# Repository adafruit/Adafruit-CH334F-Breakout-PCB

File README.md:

## Adafruit CH334F Mini USB Hub Breakouts PCB

<a href="http://www.adafruit.com/products/5997"><br/>
Click here to purchase one from the Adafruit shop</a>
<br>
<a href="http://www.adafruit.com/products/5999"><br/>
Click here to purchase one from the Adafruit shop</a>

PCB files for the Adafruit CH334F Mini USB Hub Breakouts

Format is EagleCAD schematic and board layout
* https://www.adafruit.com/product/5997
* https://www.adafruit.com/product/5999

### Description

Sometimes you've got something with USB host, like a embedded linux board, and you want to connect more than one thing. Or maybe you want to turn something like a keyboard into a multi-device USB peripheral. The Adafruit CH334F Mini 4-Port USB Hub Breakout will do that for you! it features a CH334F USB 2.1 hub chip which converts one high-speed port into four.

Most folks who use a USB hub get one that comes in an enclosure with connectors or cables included. But, those hubs are going to be bulky - they're meant for external use. This breakout board is designed to be compact, so it can easily be embedded into an enclosure or existing device. There's four mounting holes but other than that, we tried to keep it as compact as possible.

Part of how we kept it small is not including downstream ports! The breakout has either 0.1" header or USB C for the upstream, and then four 4-pin ports for peripheral connections. We expect folks to solder directly to the pads or use our 'simple' USB-breakout cables.

You get one fully assembled/tested boards and some extra header if you happen to want to plug it into a breadboard. Other than that, just keep in mind there's no USB ports for the 4 downstreams - if you need those take a look at some of the other hubs we stock.

### License

Adafruit invests time and resources providing this open source design, please support Adafruit and open-source hardware by purchasing products from [Adafruit](https://www.adafruit.com)!

Designed by Limor Fried/Ladyada for Adafruit Industries.

Creative Commons Attribution/Share-Alike, all text above must be included in any redistribution. 
See license.txt for additional details.

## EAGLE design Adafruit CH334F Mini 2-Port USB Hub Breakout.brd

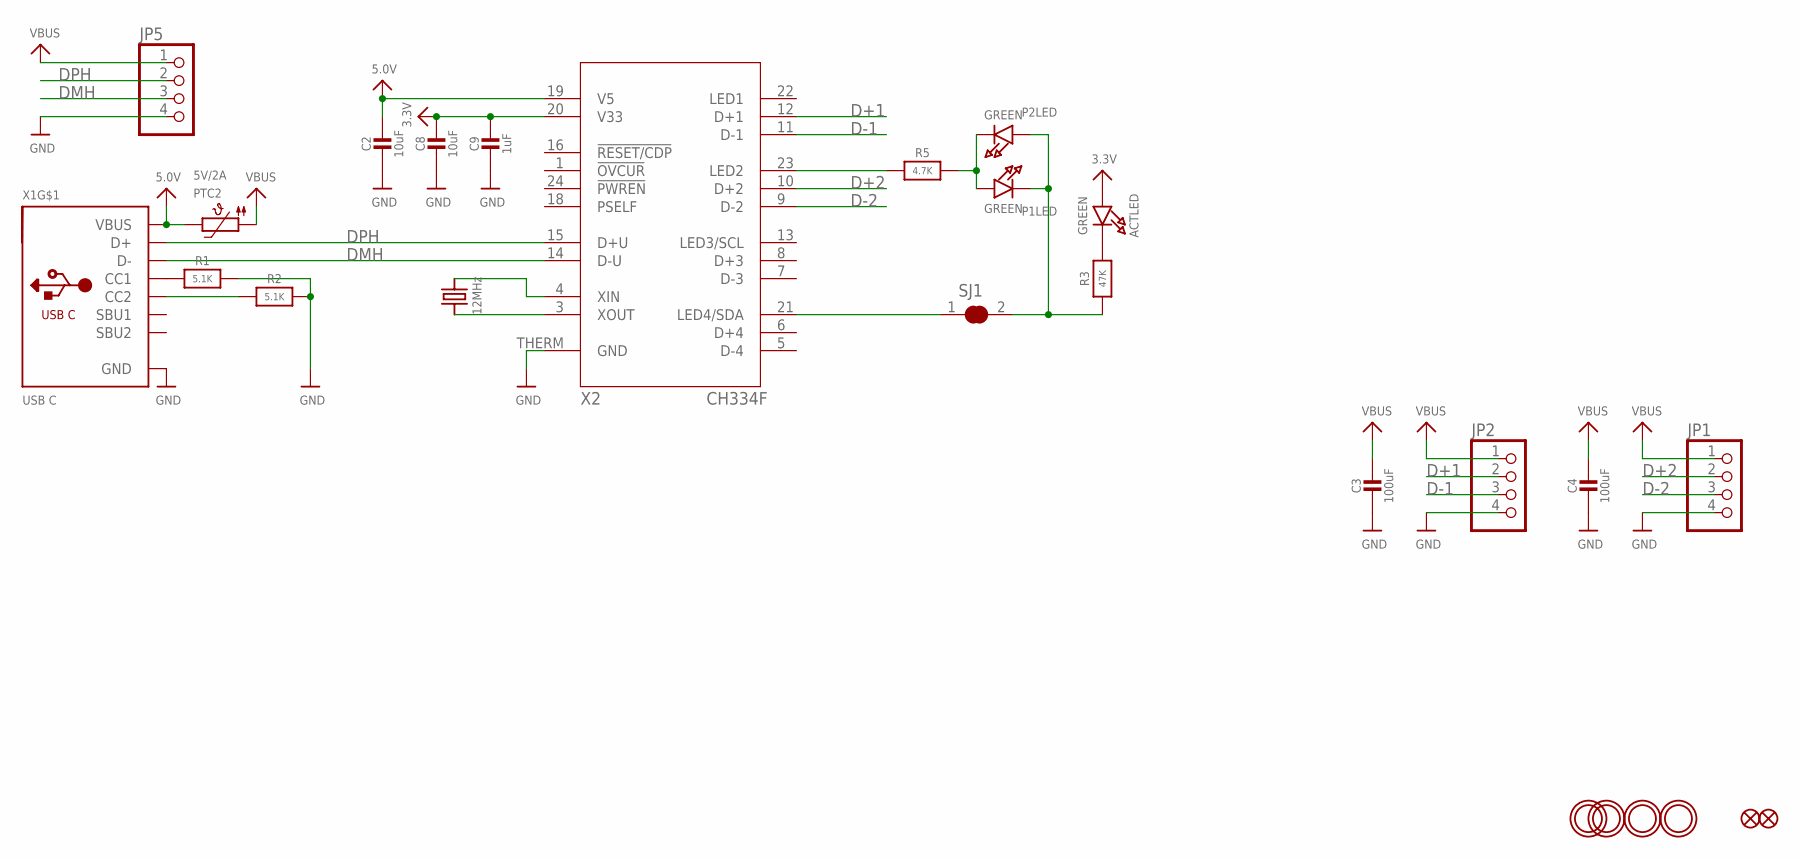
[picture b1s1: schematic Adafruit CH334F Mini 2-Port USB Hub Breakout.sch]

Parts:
ACTLED: GREEN; CHIPLED_0603_NOOUTLINE
C2, C8: 10uF; 0805-NO
C3, C4: 100uF; _1206
C9: 1uF; 0603-NO
FID1, FID2: FIDUCIAL_0.5MM
JP1, JP2, JP5: HEADER-1X4ROUND; 1X04_ROUND
P1LED, P2LED: GREEN; CHIPLED_0603_NOOUTLINE
PTC2: 5V/2A; 0805-NO
R1, R2: 5.1K; 0603-NO
R3: 47K; 0603-NO
R5: 4.7K; 0603-NO
SJ1: SOLDERJUMPER_CLOSED; SOLDERJUMPER_CLOSEDWIRE
U$23, U$28, U$29, U$31: MOUNTINGHOLE2.5; MOUNTINGHOLE_2.5_PLATED
X1: USB C; USB_C_CUSB31-CFM2AX-01-X
X2: CH334F; QFN24_4MM
Y1: 12MHz; CRYSTAL_2.5X2

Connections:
3.3V: ACTLED.A, C8.1, C9.1, X2.20 (V33)
5.0V: C2.1, PTC2.2, X1.A4B9 (VBUS), X1.B4A9 (VBUS), X2.19 (V5)
D+1: JP2.2, X2.12 (D+1)
D+2: JP1.2, X2.10 (D+2)
D-1: JP2.3, X2.11 (D-1)
D-2: JP1.3, X2.9 (D-2)
DMH: JP5.3, X1.A7 (D-), X1.B7 (D-), X2.14 (D-U)
DPH: JP5.2, X1.A6 (D+), X1.B6 (D+), X2.15 (D+U)
GND: C2.2, C3.2, C4.2, C8.2, C9.2, JP1.4, JP2.4, JP5.4, R1.2, R2.2, X1.A1B12 (GND), X1.B1A12 (GND), X2.THERM (GND)
unnamed: R1.1, X1.A5 (CC1)
unnamed: R2.1, X1.B5 (CC2)
unnamed: X2.3 (XOUT), Y1.1
unnamed: X2.4 (XIN), Y1.3 (2)
unnamed: ACTLED.C, R3.2
unnamed: P1LED.C, P2LED.A, R3.1, SJ1.2
unnamed: SJ1.1, X2.21 (LED4/SDA)
unnamed: P1LED.A, P2LED.C, R5.2
unnamed: R5.1, X2.23 (LED2)
VBUS: C3.1, C4.1, JP1.1, JP2.1, JP5.1, PTC2.1

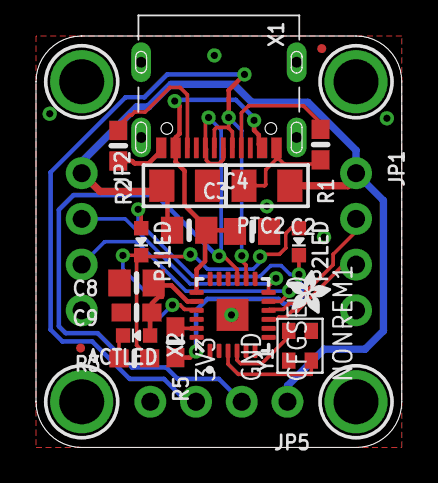
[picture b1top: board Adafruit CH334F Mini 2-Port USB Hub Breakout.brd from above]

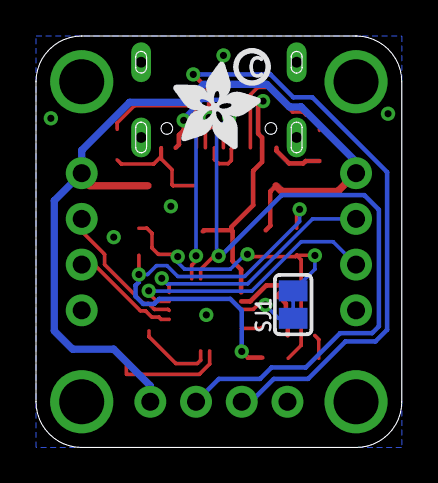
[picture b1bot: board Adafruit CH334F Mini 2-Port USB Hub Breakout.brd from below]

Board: 2 copper layers, 20.3 x 22.9 mm, 49 parts (9 on the bottom side), 19 nets.

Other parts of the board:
PLABEL0: PLABEL0
PLABEL1: PLABEL1
PLABEL3: PLABEL3
PLABEL5: PLABEL5
PLABEL6: PLABEL6
PLABEL7: PLABEL7
PLABEL8: PLABEL8
PLABEL11: PLABEL11
PLABEL13: PLABEL13
PLABEL19: PLABEL19
PLABEL21: PLABEL21
PLABEL22: PLABEL22
PLABEL23: PLABEL23
PLABEL24: PLABEL24
PLABEL26: PLABEL26
PLABEL27: PLABEL27
PLABEL30: PLABEL30
PLABEL31: PLABEL31
PLABEL32: PLABEL32
PLABEL33: PLABEL33
U$11: ADAFRUIT_2.5MM
U$33: ADAFRUIT_5MM
U$34: PCBFEAT-REV-040

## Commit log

2024-07-22 cookiecutter
2024-08-12 adding 2 port

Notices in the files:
parts and their libraries:
microbuilder: This work is placed in the public domain, and may be freely used for commercial and non-commercial work with the following conditions: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
